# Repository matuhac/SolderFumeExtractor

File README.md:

# SolderFumeExtractor

The purpose of this project is to create Fume extractor from soldering.

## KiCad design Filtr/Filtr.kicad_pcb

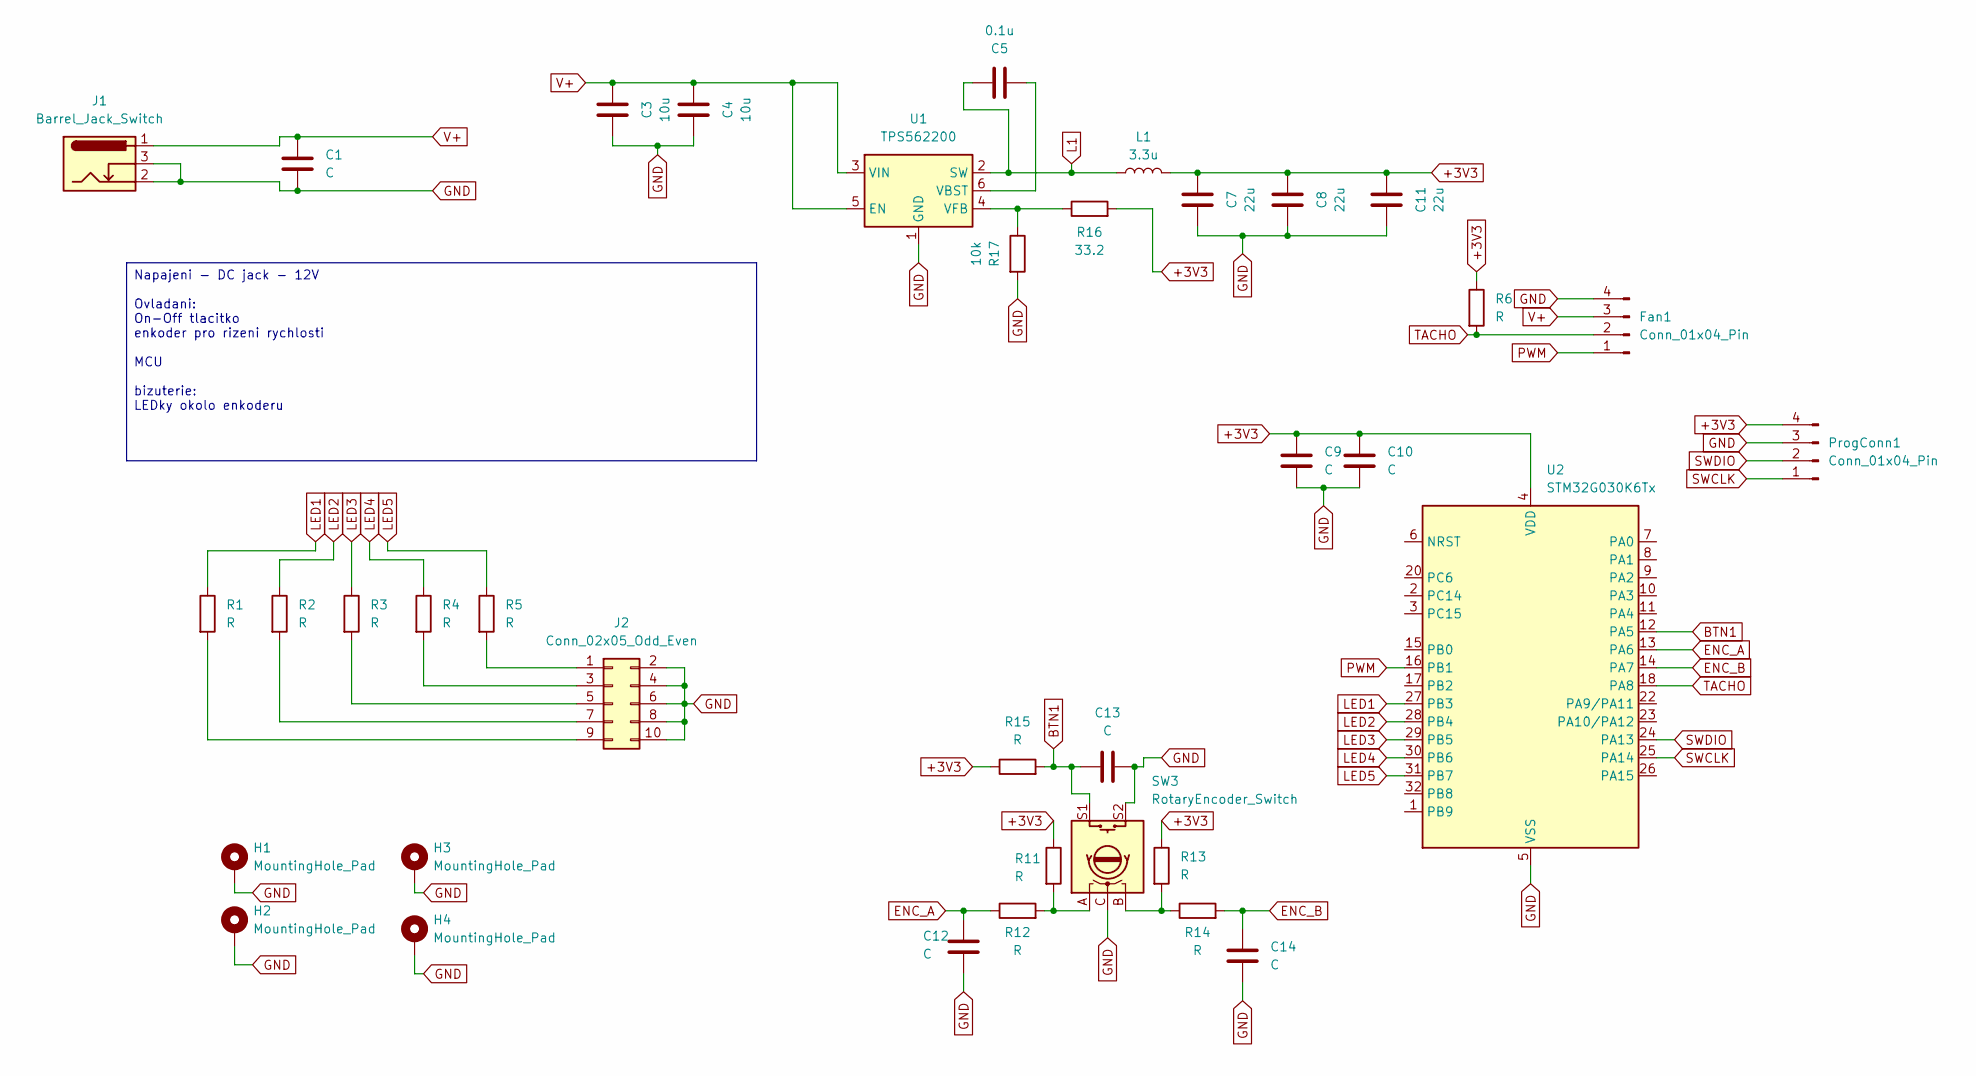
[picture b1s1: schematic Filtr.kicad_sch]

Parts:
C1: C; CP_Radial_D10.0mm_P5.00mm
C3, C4: 10u; C_1206_3216Metric
C5: 0.1u; C_1206_3216Metric
C7, C8, C11: 22u; C_0603_1608Metric
C9, C10, C12, C13, C14: C; C_0603_1608Metric
Fan1: Conn_01x04_Pin; PinHeader_1x04_P2.54mm_Vertical
H1, H2, H3, H4: MountingHole_Pad; MountingHole_3.2mm_M3_DIN965_Pad
J1: Barrel_Jack_Switch; BarrelJack_CLIFF_FC681465S_SMT_Horizontal
J2: Conn_02x05_Odd_Even; PinHeader_2x05_P2.54mm_Vertical
L1: 3.3u; L_Ferrocore_DLG-0403
ProgConn1: Conn_01x04_Pin; PinHeader_1x04_P2.54mm_Vertical
R1, R2, R3, R4, R5, R11, R12, R13, R14, R15: R; R_0603_1608Metric
R6: R; R_1206_3216Metric
R16: 33.2; R_1206_3216Metric
R17: 10k; R_1206_3216Metric
SW3: RotaryEncoder_Switch; RotaryEncoder_Alps_EC11E-Switch_Vertical_H20mm
U1: TPS562200; SOT-23-6
U2: STM32G030K6Tx; LQFP-32_7x7mm_P0.8mm

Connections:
+3V3: C7.1, C8.1, C9.1, C10.1, C11.1, L1.2, ProgConn1.4, R6.1, R11.1, R13.1, R15.1, R16.2, U2.4 (VDD)
BTN1: C13.1, R15.2, SW3.S1, U2.12 (PA5)
ENC_A: C12.2, R12.1, U2.13 (PA6)
ENC_B: C14.2, R14.2, U2.14 (PA7)
GND: C1.2, C3.2, C4.2, C7.2, C8.2, C9.2, C10.2, C11.2, C12.1, C13.2, C14.1, Fan1.4, H1.1, H2.1, H3.1, H4.1, J1.2, J1.3, J2.2, J2.4, J2.6, J2.8, J2.10, ProgConn1.3, R17.2, SW3.C, SW3.S2, U1.1 (GND), U2.5 (VSS)
L1: C5.1, L1.1, U1.2 (SW)
LED1: R1.1, U2.27 (PB3)
LED2: R2.1, U2.28 (PB4)
LED3: R3.1, U2.29 (PB5)
LED4: R4.1, U2.30 (PB6)
LED5: R5.1, U2.31 (PB7)
unnamed: J2.1, R5.2
unnamed: J2.3, R4.2
unnamed: J2.5, R3.2
unnamed: J2.7, R2.2
unnamed: J2.9, R1.2
unnamed: R11.2, R12.2, SW3.A
unnamed: R13.2, R14.1, SW3.B
unnamed: C5.2, U1.6 (VBST)
unnamed: R16.1, R17.1, U1.4 (VFB)
PWM: Fan1.1, U2.16 (PB1)
SWCLK: ProgConn1.1, U2.25 (PA14)
SWDIO: ProgConn1.2, U2.24 (PA13)
TACHO: Fan1.2, R6.2, U2.18 (PA8)
V+: C1.1, C3.1, C4.1, Fan1.3, J1.1, U1.3 (VIN), U1.5 (EN)

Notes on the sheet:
Napajeni - DC jack - 12V Ovladani: On-Off tlacitko enkoder pro rizeni rychlosti MCU bizuterie: LEDky okolo enkoderu

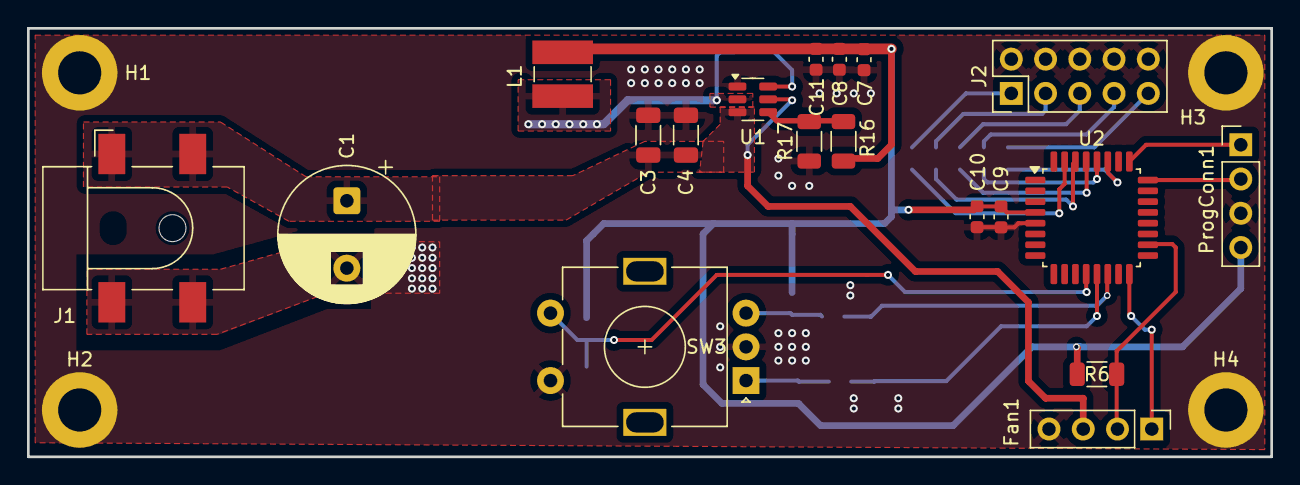
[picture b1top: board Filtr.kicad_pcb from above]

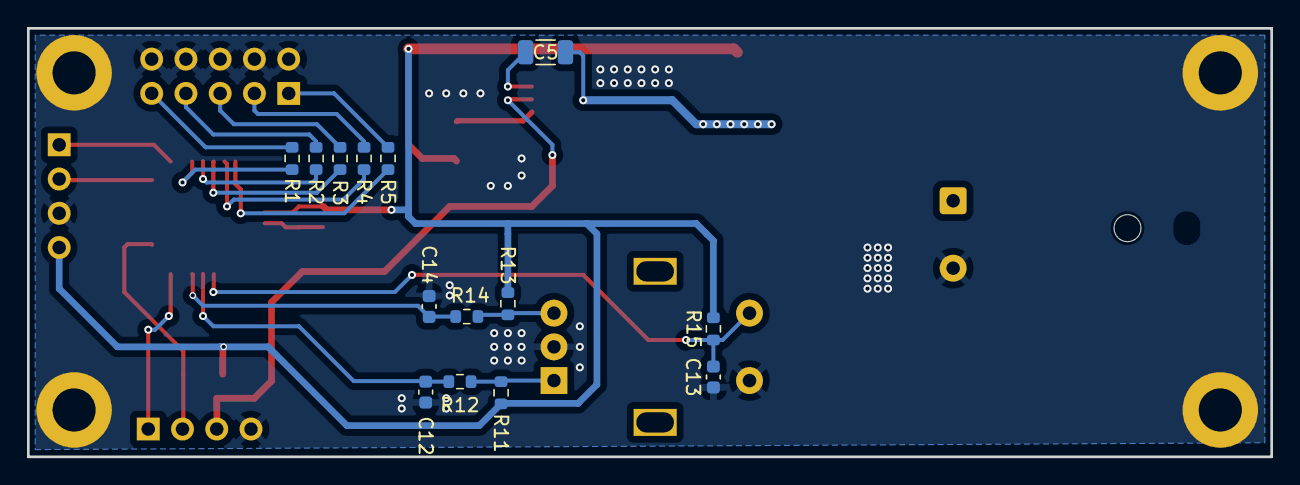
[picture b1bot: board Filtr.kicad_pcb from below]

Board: 2 copper layers, 92.2 x 31.8 mm, 37 parts (14 on the bottom side), 25 nets.

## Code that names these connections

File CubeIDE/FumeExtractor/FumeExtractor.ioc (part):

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Mcu.Name=STM32G030K(6-8)Tx
Mcu.Package=LQFP32
Mcu.UserName=STM32G030K6Tx
PA0.GPIOParameters=GPIO_Label
PA0.GPIO_Label=SER
PA0.Signal=GPIO_Output
PA1.GPIOParameters=GPIO_Label
PA1.GPIO_Label=SRCLK
PA1.Signal=GPIO_Output
PA13.Mode=Serial_Wire
PA13.Signal=SYS_SWDIO
PA14-BOOT0.Mode=Serial_Wire
PA14-BOOT0.Signal=SYS_SWCLK
PA2.GPIOParameters=GPIO_Label
PA2.GPIO_Label=RCLK
PA2.Signal=GPIO_Output
PA5.GPIOParameters=GPIO_Label
PA5.GPIO_Label=BTN1
PA5.Signal=GPIO_Input
PA6.GPIOParameters=GPIO_Label
PA6.GPIO_Label=ENC_A
PA6.Signal=S_TIM3_CH1
PA7.GPIOParameters=GPIO_Label
PA7.GPIO_Label=ENC_B
PA7.Signal=S_TIM3_CH2
PA8.GPIOParameters=GPIO_Label
PA8.GPIO_Label=TACHO
PA8.Signal=S_TIM1_CH1
PB1.GPIOParameters=GPIO_Label
PB1.GPIO_Label=PWM_FAN
PB1.Signal=S_TIM14_CH1
PB3.GPIOParameters=GPIO_Label
PB3.GPIO_Label=LED1
PB3.Signal=GPIO_Output
PB4.GPIOParameters=GPIO_Label
PB4.GPIO_Label=LED2
PB4.Signal=GPIO_Output
PB5.GPIOParameters=GPIO_Label
PB5.GPIO_Label=LED3
PB5.Signal=GPIO_Output
PB6.GPIOParameters=GPIO_Label
PB6.GPIO_Label=LED4
PB6.Signal=GPIO_Output
PB7.GPIOParameters=GPIO_Label
PB7.GPIO_Label=LED5
PB7.Signal=GPIO_Output
RCC.HSE_VALUE=8000000
RCC.SYSCLKFreq_VALUE=16000000
board=custom

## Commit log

2026-04-13 Pridani Kicadu a CubeIDE.
    Pridanu uz vytvorenych souboru.
2026-04-13 Readme
2026-04-13 Kicad - pridani bargarfu a shiftregistru
2026-04-13 Vymazani CubeIDE
2026-04-13 Vytvoreni CubeIDE, konfiguarce casovacu.
2026-04-13 CubeIDE a Kicad
    CubeIDE -nastaveni pinu
    Kicad - pridani shift registru
2026-05-22 Novy Design desky
